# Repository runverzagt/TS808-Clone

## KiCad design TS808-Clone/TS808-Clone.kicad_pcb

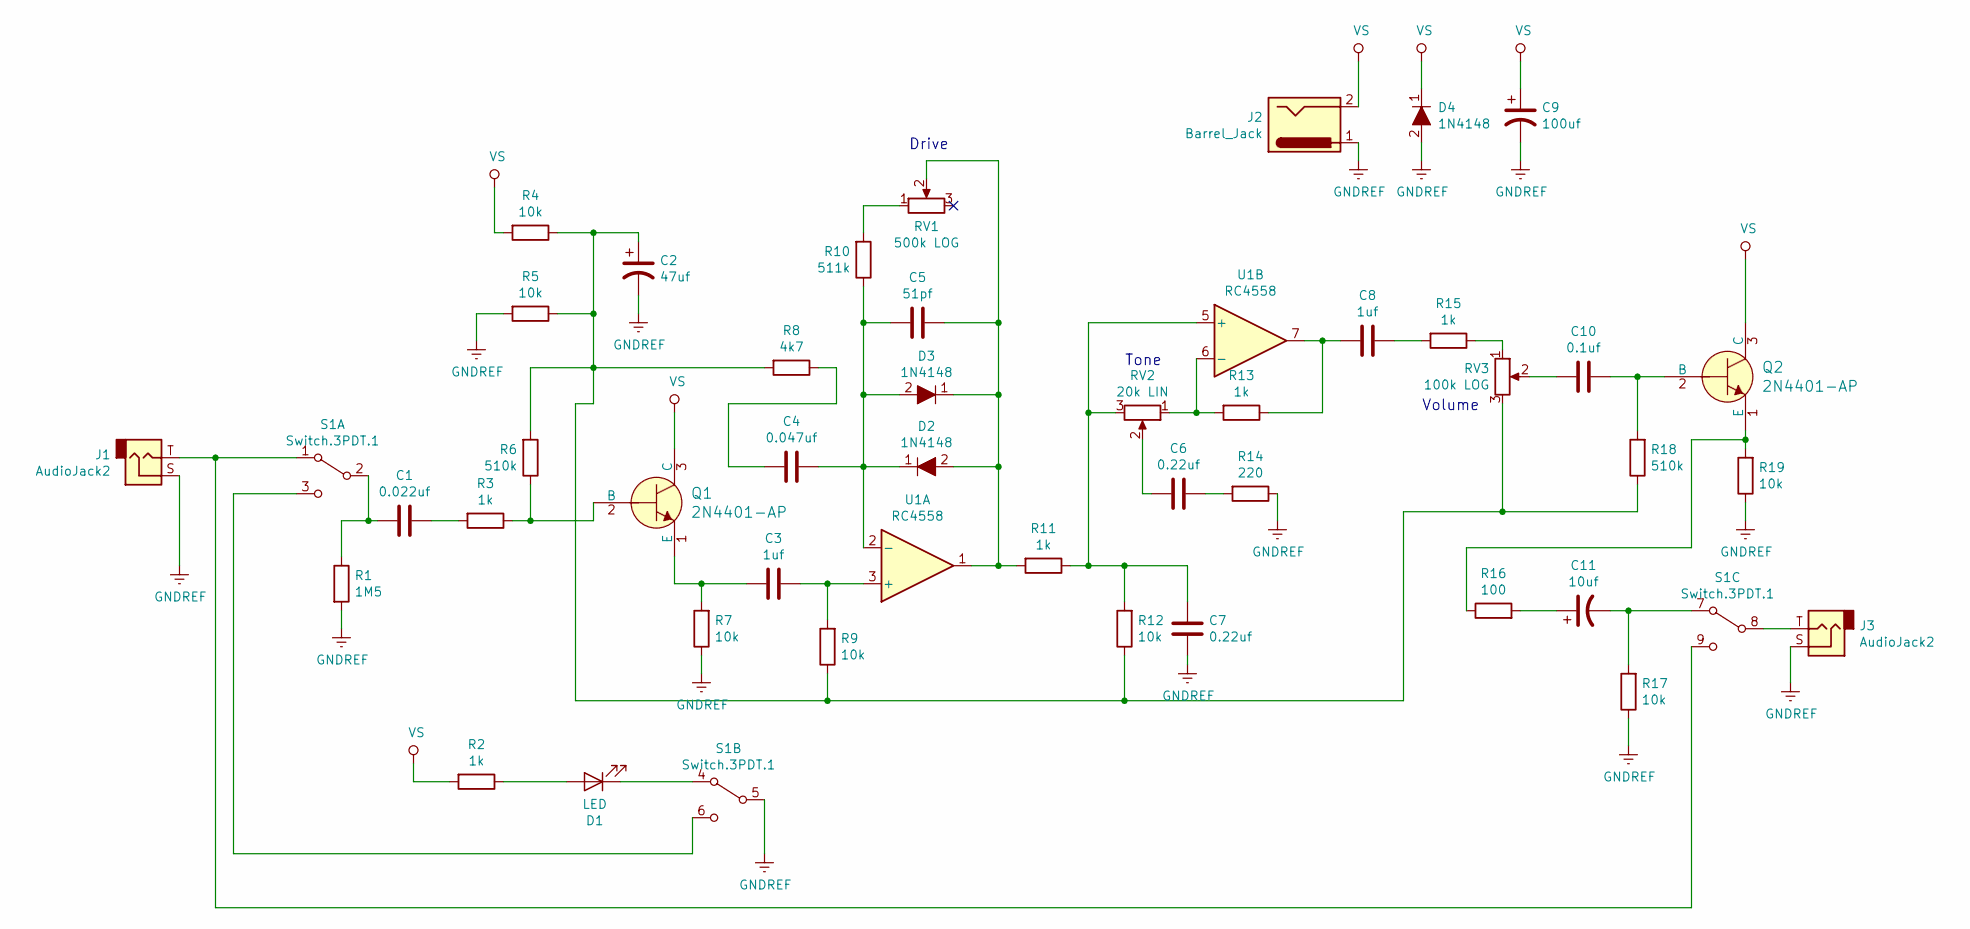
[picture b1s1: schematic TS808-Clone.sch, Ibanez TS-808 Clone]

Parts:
C1: 0.022uf; C_Axial_L3.8mm_D2.6mm_P7.50mm_Horizontal
C2: 47uf; CP_Radial_D5.0mm_P2.00mm
C3, C8: 1uf; C_Rect_L7.0mm_W3.5mm_P5.00mm
C4: 0.047uf; C_Rect_L7.0mm_W2.5mm_P5.00mm
C5: 51pf; C_Rect_L5.0mm_W3.2mm_P2.50mm
C6, C7: 0.22uf; C_Rect_L7.0mm_W4.5mm_P5.00mm
C9: 100uf; CP_Radial_D6.3mm_P2.50mm
C10: 0.1uf; C_Axial_L3.8mm_D2.6mm_P7.50mm_Horizontal
C11: 10uf; CP_Radial_D5.0mm_P2.00mm
D1: LED; LED_D5.0mm
D2, D3, D4: 1N4148; Diode_DO-35_P10mm; MPN 1N4148; Digi-Key_PN 1N4148FS-ND
J1, J3: AudioJack2; Headphone_Jack_6.35mm_RA49B11
J2: Barrel_Jack; BarrelJack_Horiz_55X21_THT
Q1, Q2: 2N4401-AP; TO-92-3_Formed_Leads; MPN 2N4401-AP; Digi-Key_PN 2N4401-APCT-ND
R1: 1M5; R_Axial_DIN0207_L6.3mm_D2.5mm_P7.62mm_Horizontal
R2, R3, R11, R13, R15: 1k; R_Axial_DIN0207_L6.3mm_D2.5mm_P7.62mm_Horizontal
R4, R5, R7, R9, R12, R17, R19: 10k; R_Axial_DIN0207_L6.3mm_D2.5mm_P7.62mm_Horizontal
R6, R18: 510k; R_Axial_DIN0207_L6.3mm_D2.5mm_P7.62mm_Horizontal
R8: 4k7; R_Axial_DIN0207_L6.3mm_D2.5mm_P7.62mm_Horizontal
R10: 511k; R_Axial_DIN0207_L6.3mm_D2.5mm_P7.62mm_Horizontal
R14: 220; R_Axial_DIN0207_L6.3mm_D2.5mm_P7.62mm_Horizontal
R16: 100; R_Axial_DIN0207_L6.3mm_D2.5mm_P7.62mm_Horizontal
RV1: 500k LOG; Potentiometer_Bourns_PTV09A-1_Single_Vertical
RV2: 20k LIN; Potentiometer_Bourns_PTV09A-1_Single_Vertical
RV3: 100k LOG; Potentiometer_Bourns_PTV09A-1_Single_Vertical
S1: Switch.3PDT.1; Switch_3P3T_Footswitch_PC_THT
U1: RC4558; DIP-8_W7.62mm

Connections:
GNDREF: C2.2, C7.1, C9.2, D4.2, J1.S, J2.1, J3.S, R1.2, R5.2, R7.1, R14.1, R17.1, R19.1, S1.5 (E), U1.4 (V-)
unnamed: C1.1, R3.2
unnamed: C1.2, R1.1, S1.2 (B)
unnamed: C2.1, R4.1, R5.1, R6.2, R8.2, R9.1, R12.1, R18.1, RV3.3
unnamed: C3.1, R9.2, U1.3 (+)
unnamed: C3.2, Q1.1 (E), R7.2
unnamed: C4.1, C5.2, D2.1, D3.2, R10.1, U1.2 (-)
unnamed: C4.2, R8.1
unnamed: C5.1, D2.2, D3.1, R11.2, RV1.2, U1.1
unnamed: C6.1, RV2.2
unnamed: C6.2, R14.2
unnamed: C7.2, R11.1, R12.2, RV2.3, U1.5 (+)
unnamed: C8.1, R13.1, U1.7
unnamed: C8.2, R15.2
unnamed: C10.1, RV3.2
unnamed: C10.2, Q2.2 (B), R18.2
unnamed: C11.1, R16.2
unnamed: C11.2, R17.2, S1.7 (G)
unnamed: D1.1 (K), S1.4 (D)
unnamed: D1.2 (A), R2.1
unnamed: J1.T, S1.1 (A), S1.9 (I)
unnamed: J3.T, S1.8 (H)
unnamed: Q1.2 (B), R3.1, R6.1
unnamed: Q2.1 (E), R16.1, R19.2
unnamed: R10.2, RV1.1
unnamed: R13.2, RV2.1, U1.6 (-)
unnamed: R15.1, RV3.1
unnamed: S1.3 (C), S1.6 (F)
VS: C9.1, D4.1, J2.2, Q1.3 (C), Q2.3 (C), R2.2, R4.2, U1.8 (V+)

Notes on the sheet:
Drive
Tone
Volume

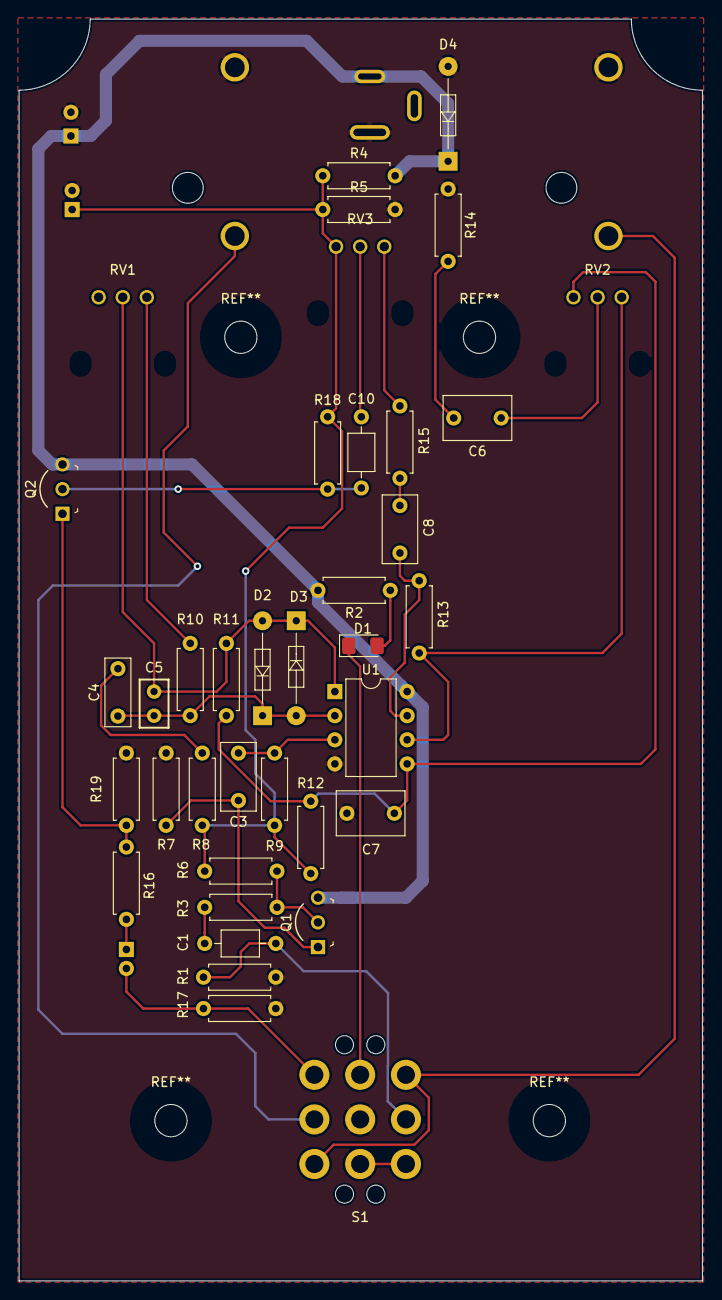
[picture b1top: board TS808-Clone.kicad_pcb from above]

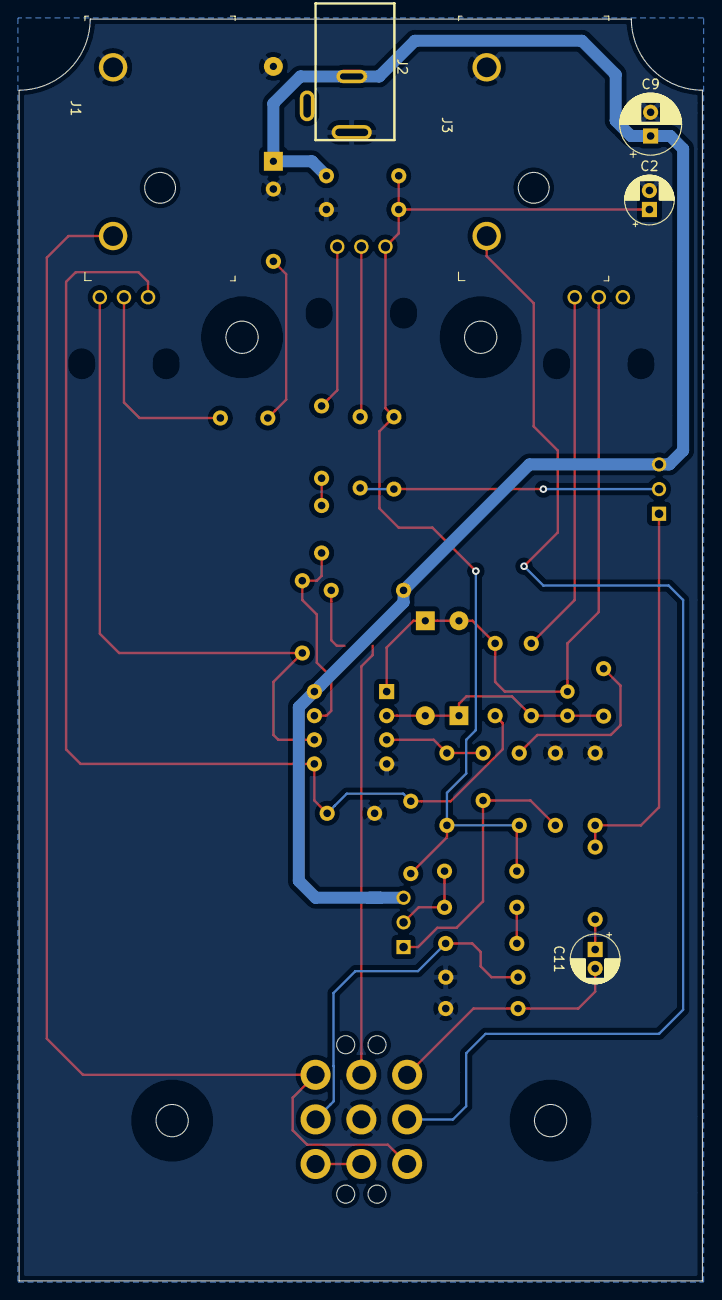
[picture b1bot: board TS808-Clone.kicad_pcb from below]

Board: 2 copper layers, 72.0 x 133.0 mm, 44 parts (6 on the bottom side), 29 nets.

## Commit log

2019-11-13 Generally rearranged tracks and a couple componenets. Removed holes.
    Is now cleaner. Holes+standoffs were not needed because the pots are panel mount.
2019-11-14 Finished traces. Added fill with ground layer.
2019-11-15 trying a redesign of the layout
2019-11-26 changed footprint for the pots
2019-12-03 moved jacks to final positions
2019-12-05 Tentative final design
